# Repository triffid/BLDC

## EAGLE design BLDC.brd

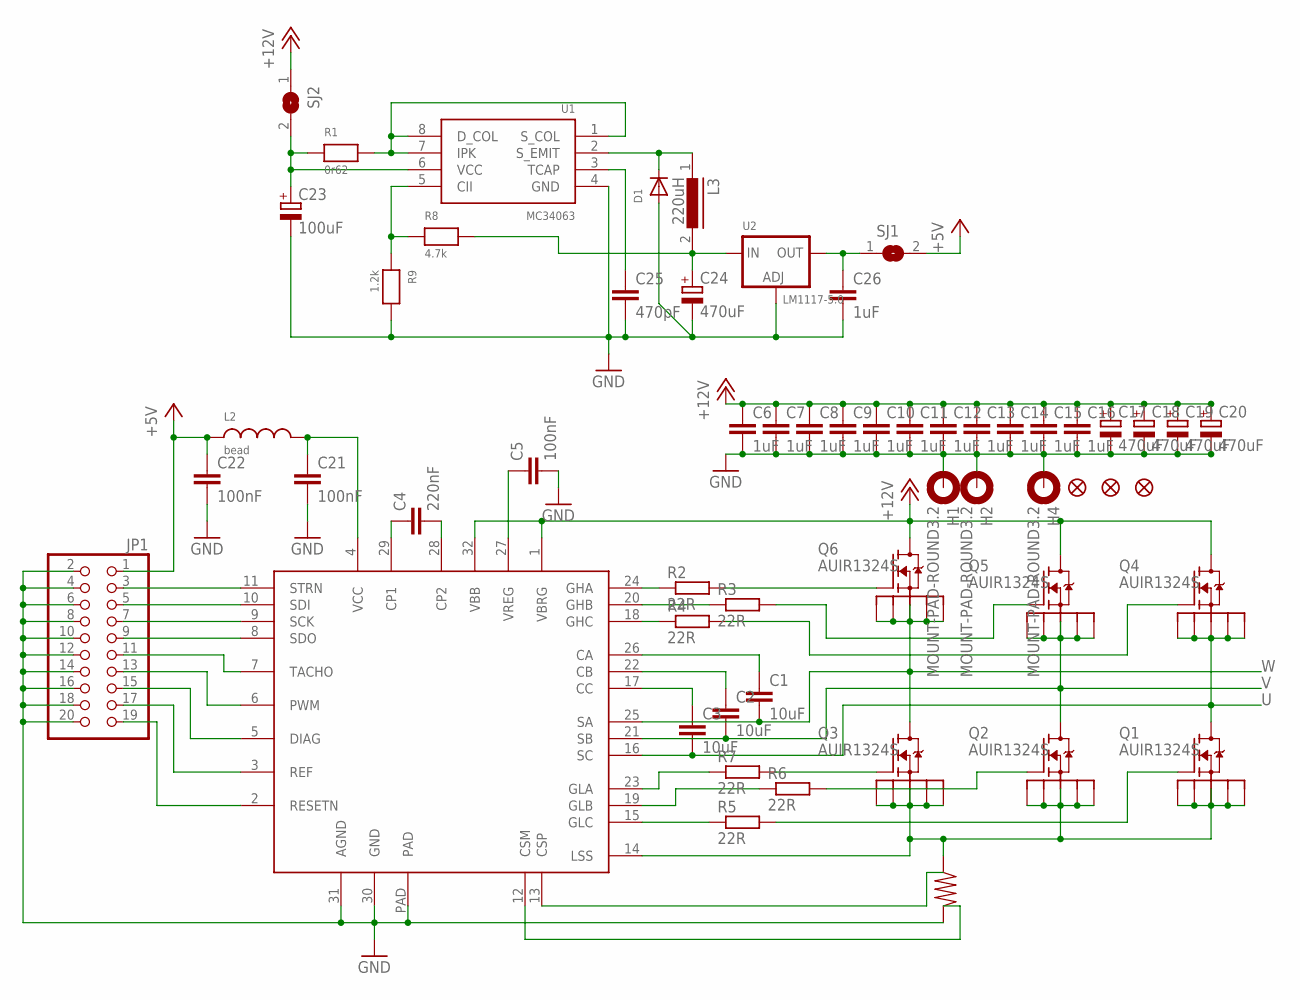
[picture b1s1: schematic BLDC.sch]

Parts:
C1, C2, C3: 10uF; C0603K
C4: 220nF; C0603K
C5, C21, C22: 100nF; C0603K
C6, C7, C8, C9, C10, C11, C12, C13, C14, C15, C16, C26: 1uF; C0603K
C17, C18, C19, C20, C24: 470uF; PANASONIC_D
C23: 100uF; PANASONIC_D
C25: 470pF; C0603K
D1: DIODESOD-123; SOD-123
H1, H2, H4: MOUNT-PAD-ROUND3.2; 3,2-PAD
IC1: A4960; LQFP32-7X7
JP1: PINHD-2X10; 2X10
JP2, JP3, JP4: FIDUCIAL1X2; FIDUCIAL-1X2
L2: bead; 0603
L3: 220uH; SLF7045
Q1, Q2, Q3, Q4, Q5, Q6: AUIR1324S; D2PAK-7
R1: 0r62; 0603
R2, R3, R4, R5, R6, R7: 22R; R0603
R8: 4.7k; 0603
R9: 1.2k; 0603
SJ1, SJ2: SOLDERJUMPERREFLOW; SOLDERJUMPER_REFLOW
U1: MC34063; SOIC8
U2: LM1117-5.0; SOT223-R

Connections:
+5V: C22.1, JP1.1, L2.1, SJ1.2
+12V: C6.1, C7.1, C8.1, C9.1, C10.1, C11.1, C12.1, C13.1, C14.1, C15.1, C16.1, C17.+, C18.+, C19.+, C20.+, IC1.1 (VBRG), IC1.32 (VBB), Q4.D, Q5.D, Q6.D, SJ2.1
CSM: IC1.12 (CSM)
CSP: IC1.14 (LSS), Q1.S1, Q1.S2, Q1.S3, Q1.S4, Q1.S5, Q2.S1, Q2.S2, Q2.S3, Q2.S4, Q2.S5, Q3.S1, Q3.S2, Q3.S3, Q3.S4, Q3.S5
GND: C5.2, C6.2, C7.2, C8.2, C9.2, C10.2, C11.2, C12.2, C13.2, C14.2, C15.2, C16.2, C17.-, C18.-, C19.-, C20.-, C21.2, C22.2, C23.-, C24.-, C25.2, C26.2, D1.A, H1.B3,2, H2.B3,2, H4.B3,2, IC1.30 (GND), IC1.31 (AGND), IC1.PAD, JP1.2, JP1.4, JP1.6, JP1.8, JP1.10, JP1.12, JP1.14, JP1.16, JP1.18, JP1.20, R9.2, U1.4 (GND), U2.1 (ADJ)
unnamed: Q6.G, R2.2
unnamed: IC1.11 (STRN), JP1.3
unnamed: IC1.10 (SDI), JP1.5
unnamed: IC1.9 (SCK), JP1.7
unnamed: Q3.G, R7.2
unnamed: Q2.G, R6.2
unnamed: Q1.G, R5.2
unnamed: IC1.24 (GHA), R2.1
unnamed: Q5.G, R3.2
unnamed: Q4.G, R4.2
unnamed: IC1.20 (GHB), R3.1
unnamed: IC1.18 (GHC), R4.1
unnamed: IC1.23 (GLA), R7.1
unnamed: C1.1, IC1.26 (CA)
unnamed: C2.1, IC1.22 (CB)
unnamed: C3.1, IC1.17 (CC)
unnamed: C4.1, IC1.29 (CP1)
unnamed: C4.2, IC1.28 (CP2)
unnamed: IC1.19 (GLB), R6.1
unnamed: IC1.15 (GLC), R5.1
unnamed: C5.1, IC1.27 (VREG)
unnamed: C21.1, IC1.4 (VCC), L2.2
unnamed: R1.2, U1.1 (S_COL), U1.7 (IPK), U1.8 (D_COL)
unnamed: D1.C, L3.1, U1.2 (S_EMIT)
unnamed: IC1.8 (SDO), JP1.9
unnamed: IC1.7 (TACHO), JP1.11
unnamed: IC1.6 (PWM), JP1.13
unnamed: IC1.5 (DIAG), JP1.15
unnamed: IC1.3 (REF), JP1.17
unnamed: IC1.2 (RESETN), JP1.19
unnamed: C24.+, L3.2, R8.2, U2.3 (IN)
unnamed: C26.1, SJ1.1, U2.2 (OUT)
unnamed: C23.+, R1.1, SJ2.2, U1.6 (VCC)
unnamed: C25.1, U1.3 (TCAP)
unnamed: R8.1, R9.1, U1.5 (CII)
U: C3.2, IC1.16 (SC), Q1.D, Q4.S1, Q4.S2, Q4.S3, Q4.S4, Q4.S5
V: C2.2, IC1.21 (SB), Q2.D, Q5.S1, Q5.S2, Q5.S3, Q5.S4, Q5.S5
W: C1.2, IC1.25 (SA), Q3.D, Q6.S1, Q6.S2, Q6.S3, Q6.S4, Q6.S5

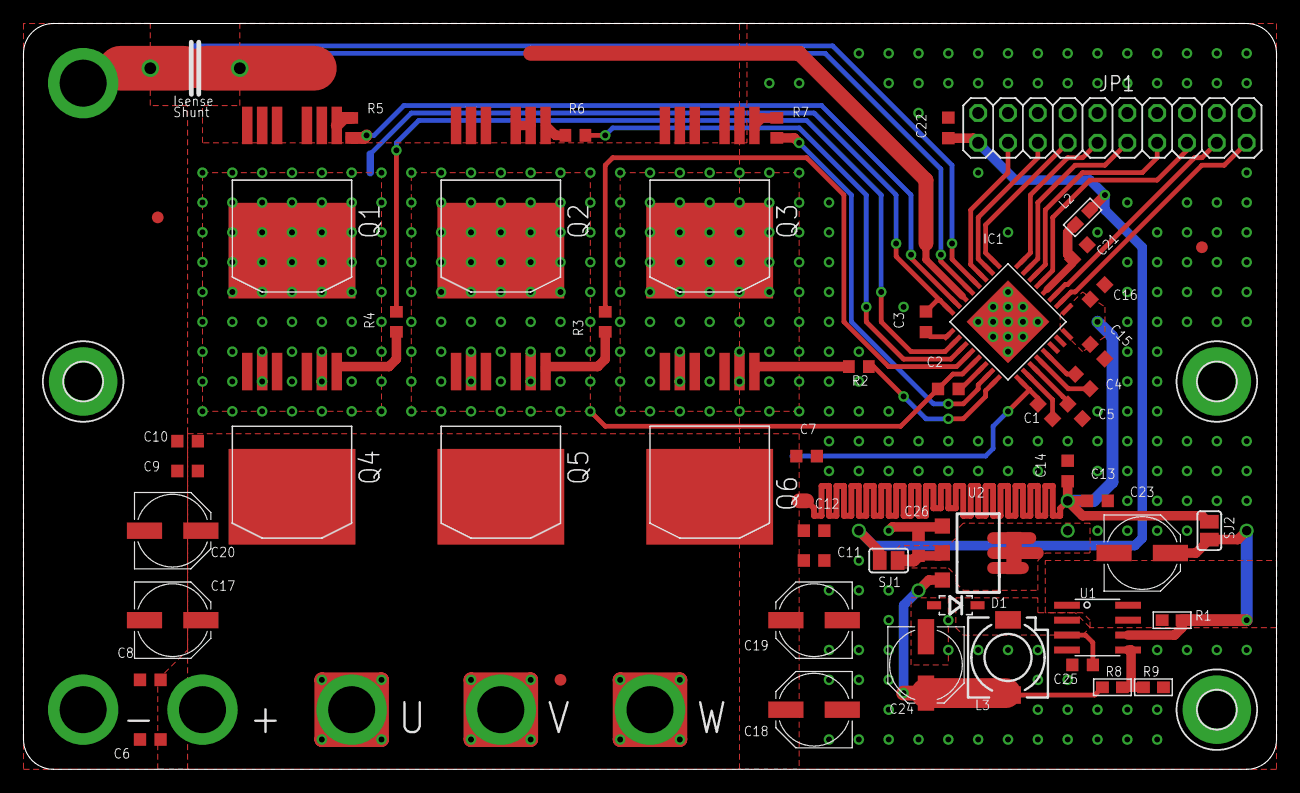
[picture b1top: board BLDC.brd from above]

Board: 2 copper layers, 106.7 x 63.5 mm, 56 parts (0 on the bottom side), 42 nets.

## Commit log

2013-02-07 change some values, move R5 to reduce risk of shorting it

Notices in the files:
parts and their libraries:
microbuilder: This work is placed in the public domain, and may be freely used for commercial and non-commercial work with the following conditions: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
SparkFun: Licensing: CC v3.0 Share-Alike You are welcome to use this library for commercial purposes.
